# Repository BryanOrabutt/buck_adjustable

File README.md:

# buck_adjustable
An adjustable buck converter.

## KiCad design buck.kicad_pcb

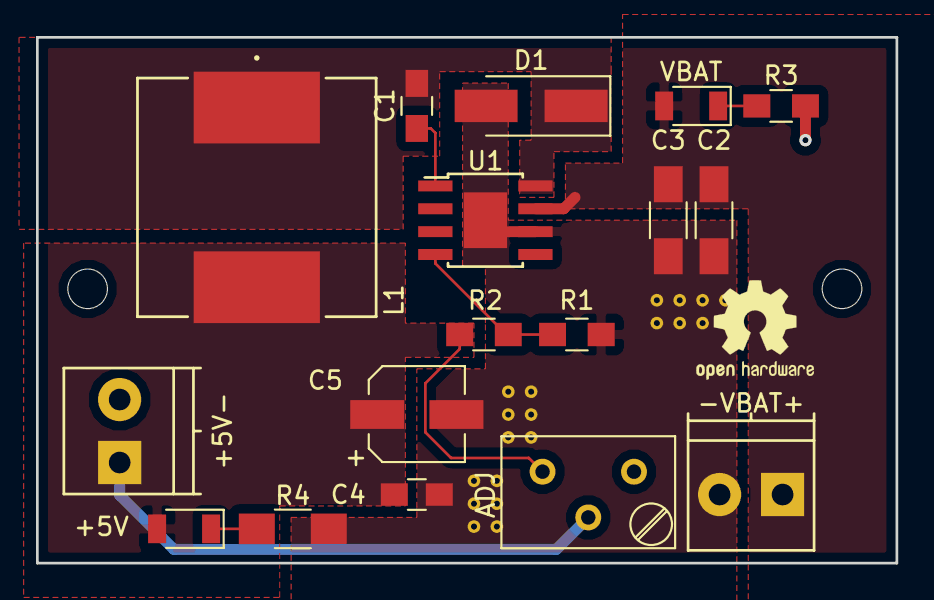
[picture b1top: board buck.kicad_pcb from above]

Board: 2 copper layers, 47.8 x 29.2 mm, 17 parts (0 on the bottom side), 9 nets.

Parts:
+5V: LED; D_1206
+5V-: -5V+; TerminalBlock_Pheonix_PT-3.5mm_2pol
-VBAT+: -VBAT+; TerminalBlock_Pheonix_PT-3.5mm_2pol
ADJ: POT; Potentiometer_Trimmer_Bourns_3299Y
C1: 10nF; C_0805_HandSoldering
C2, C3: 4.7uF; C_1206_HandSoldering
C4: 100nF; C_0805_HandSoldering
C5: 220uF; CP_Elec_5x5.3
D1: STPS5L60U; D_SMA_Handsoldering
L1: 22uH; SRR1208-220ML
R1: 10K; R_0805_HandSoldering
R2: 1K; R_0805_HandSoldering
R3: 2K; R_0805_HandSoldering
R4: 220; R_1206_HandSoldering
U1: TPS5430; TI_SO-PowerPAD-8
VBAT: LED; D_1206

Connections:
+5V: +5V.2, +5V-.1, ADJ.2, C4.1, C5.1, L1.2
+BATT: -VBAT+.1, C2.1, C3.1, U1.7, VBAT.2
/PH: C1.2, D1.1, L1.1, U1.8
GND: +5V-.2, -VBAT+.2, C2.2, C3.2, C4.2, C5.2, D1.2, R1.2, R3.2, R4.2, U1.6, U1.9
unnamed: C1.1, U1.1
unnamed: R3.1, VBAT.1
unnamed: +5V.1, R4.1
unnamed: ADJ.3, R2.1
unnamed: R1.1, R2.2, U1.4

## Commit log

2017-09-29 removed backup
2017-09-29 Adjusted silk screen
2017-09-29 Fixed bottom silk
2017-09-29 Added mounting holes
2017-09-29 Moved vias

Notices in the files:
parts and their libraries:
Copyright 2016 Accelerated Designs. All rights reserved.
